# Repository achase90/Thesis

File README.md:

Thesis
======

Folder for my thesis

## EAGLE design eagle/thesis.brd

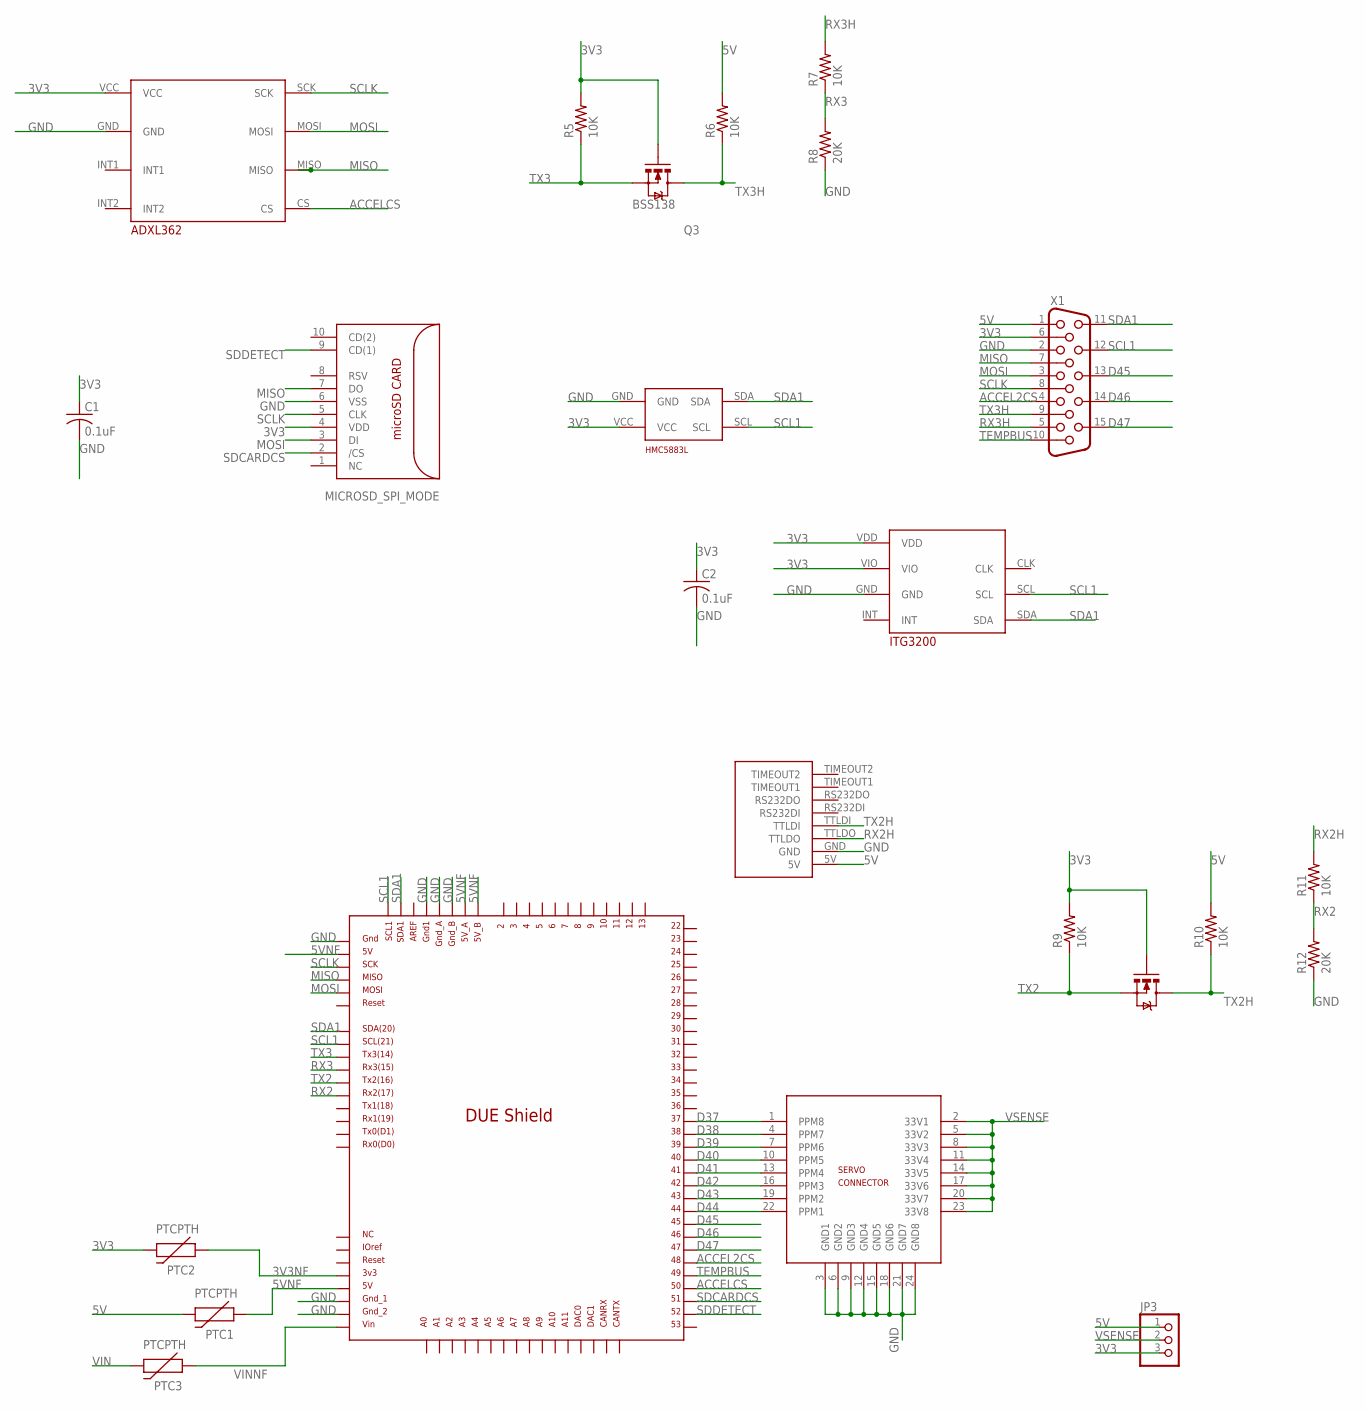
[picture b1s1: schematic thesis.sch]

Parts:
C1, C2: 0.1uF; C0603
JP3: PINHD-1X3; 1X03
PTC1, PTC2, PTC3: PTCPTH; PTC
Q1, Q3: BSS138; SOT23
R5, R6, R7, R9, R10, R11: 10K; R0603
R8, R12: 20K; R0603
U$1: DUE(NORMAL)
U$2: MICROSD_SPI_MODE; MICRO_SD_CONNECTOR
U$4: HMC5883L
U$5: HEADER-3X8SERVO; 3X8RA
U$6: UBLOXLEA6TBOB
U$7: ITG3200
U$8: ADXL362
X1: HF15V; HDF15V

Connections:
3V3: C1.1, C2.1, JP3.3, PTC2.P$2 (2), Q1.1 (G), Q3.1 (G), R5.2, R9.2, U$2.4 (VDD), U$4.VCC, U$7.VDD, U$7.VIO, U$8.VCC, X1.6
3V3NF: PTC2.P$1 (1), U$1.3V3
5V: JP3.1, PTC1.P$2 (2), R6.2, R10.2, U$6.5V, X1.1
5VNF: PTC1.P$1 (1), U$1.5V, U$1.5V_A, U$1.5V_B, U$1.GND_ICSP
ACCEL2CS: U$1.48, X1.4
ACCELCS: U$1.50, U$8.CS
D37: U$1.37, U$5.1 (PPM8)
D38: U$1.38, U$5.4 (PPM7)
D39: U$1.39, U$5.7 (PPM6)
D40: U$1.40, U$5.10 (PPM5)
D41: U$1.41, U$5.13 (PPM4)
D42: U$1.42, U$5.16 (PPM3)
D43: U$1.43, U$5.19 (PPM2)
D44: U$1.44, U$5.22 (PPM1)
D45: U$1.45, X1.13
D46: U$1.46, X1.14
D47: U$1.47, X1.15
GND: C1.2, C2.2, R8.1, R12.1, U$1.5V_ICSP, U$1.GND1, U$1.GND_1, U$1.GND_2, U$1.GND_A, U$1.GND_B, U$2.6 (VSS), U$4.GND, U$5.3 (GND1), U$5.6 (GND2), U$5.9 (GND3), U$5.12 (GND4), U$5.15 (GND5), U$5.18 (GND6), U$5.21 (GND7), U$5.24 (GND8), U$6.GND, U$7.GND, U$8.GND, X1.2
MISO: U$1.MISO_ICSP, U$2.7 (DO), U$8.MISO, X1.7
MOSI: U$1.MOSI_ICSP, U$2.3 (DI), U$8.MOSI, X1.3
RX2: R11.1, R12.2, U$1.RX2
RX2H: R11.2, U$6.TTLDO
RX3: R7.1, R8.2, U$1.RX3
RX3H: R7.2, X1.5
SCL1: U$1.SCL, U$1.SCL1, U$4.SCL, U$7.SCL, X1.12
SCLK: U$1.SCK_ICSP, U$2.5 (CLK), U$8.SCK, X1.8
SDA1: U$1.SDA, U$1.SDA1, U$4.SDA, U$7.SDA, X1.11
SDCARDCS: U$1.51, U$2.2 (/CS)
SDDETECT: U$1.52, U$2.9 (CD(1))
TEMPBUS: U$1.49, X1.10
TX2: Q1.2 (S), R9.1, U$1.TX2
TX2H: Q1.3 (D), R10.1, U$6.TTLDI
TX3: Q3.2 (S), R5.1, U$1.TX3
TX3H: Q3.3 (D), R6.1, X1.9
VIN: PTC3.P$2 (2)
VINNF: PTC3.P$1 (1), U$1.VIN
VSENSE: JP3.2, U$5.2 (33V1), U$5.5 (33V2), U$5.8 (33V3), U$5.11 (33V4), U$5.14 (33V5), U$5.17 (33V6), U$5.20 (33V7), U$5.23 (33V8)

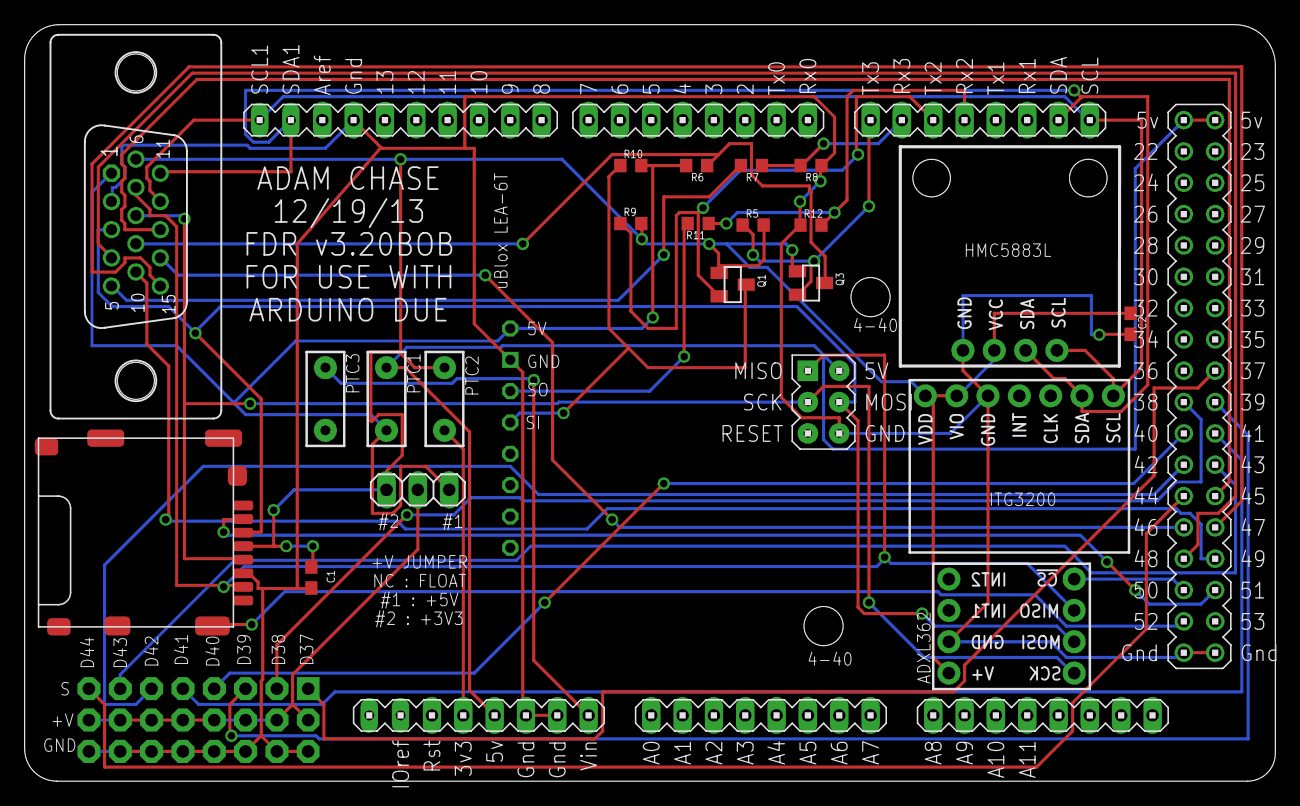
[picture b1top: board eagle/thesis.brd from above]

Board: 2 copper layers, 101.4 x 61.3 mm, 24 parts (0 on the bottom side), 36 nets.

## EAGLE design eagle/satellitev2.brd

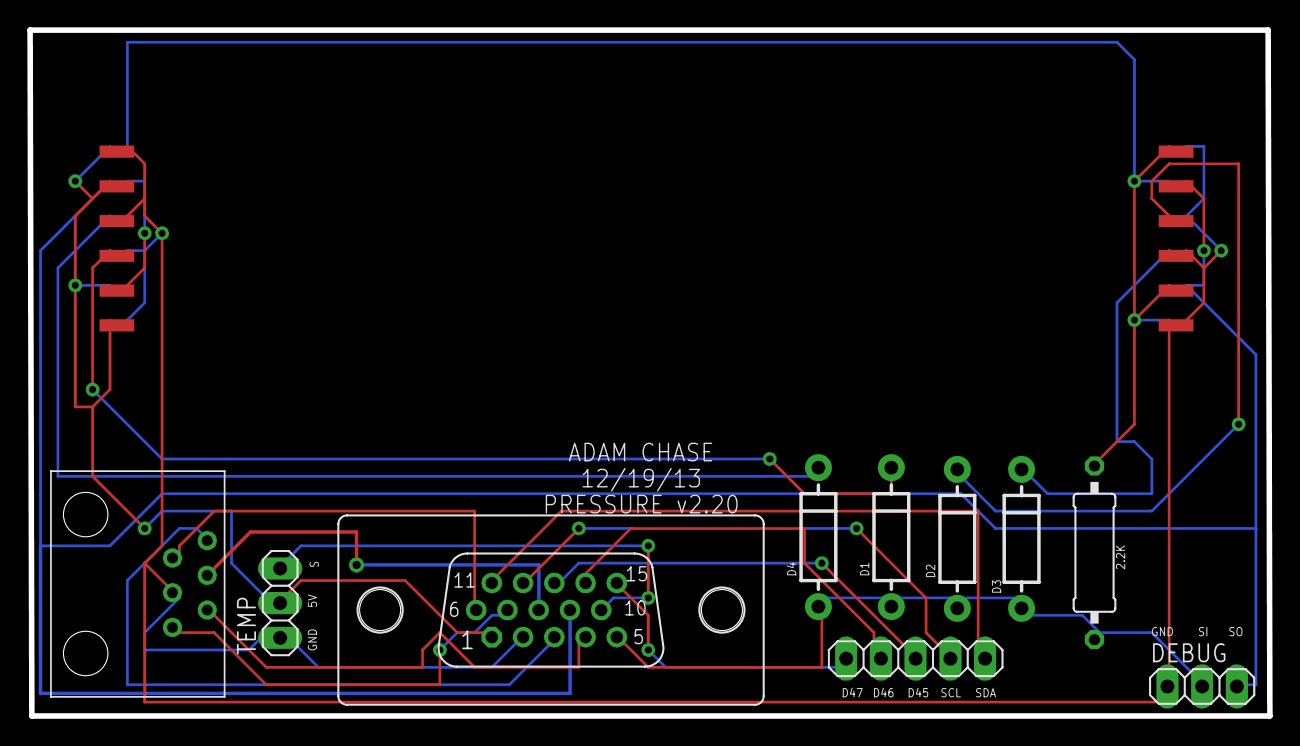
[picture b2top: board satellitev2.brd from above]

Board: 2 copper layers, 90.7 x 50.2 mm, 14 parts (0 on the bottom side), 19 nets.

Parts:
D1, D2, D3, D4: DIODE-1N4001
DEBUG: 1X03
JP1: 1X05
R1: 2.2K; 0309/12
TEMP: 1X03
U$1, U$2: 1X6SMDPINS
U$3, U$4: 1X6SMDPINSB
U$5: RJ11V
X1: HDF15V

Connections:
3V3: U$5.P$6, X1.6
5V: R1.1, TEMP.2, U$1.P$2, U$1.P$6, U$2.P$1, U$2.P$5, U$3.P$2, U$3.P$6, U$4.P$1, U$4.P$5, X1.1
ACCEL2CS: U$5.P$1, X1.4
D45: JP1.3, X1.13
D46: JP1.4, X1.14
D47: JP1.5, X1.15
GND: DEBUG.1, TEMP.1, U$1.P$1, U$1.P$3, U$2.P$4, U$2.P$6, U$3.P$1, U$3.P$3, U$4.P$4, U$4.P$6, U$5.P$5, X1.2
MISO: U$5.P$4, X1.7
MOSI: U$5.P$3, X1.3
unnamed: D2.C, U$2.P$3
unnamed: D1.C, U$1.P$4
unnamed: D4.C, U$4.P$3
unnamed: D3.C, U$3.P$4
RX: DEBUG.3, U$1.P$5, U$2.P$2, U$3.P$5, U$4.P$2, X1.9
SCL: JP1.2, X1.12
SCLK: U$5.P$2, X1.8
SDA: JP1.1, X1.11
TEMPBUS: TEMP.3, X1.10
TX: D1.A, D2.A, D3.A, D4.A, DEBUG.2, R1.2, X1.5

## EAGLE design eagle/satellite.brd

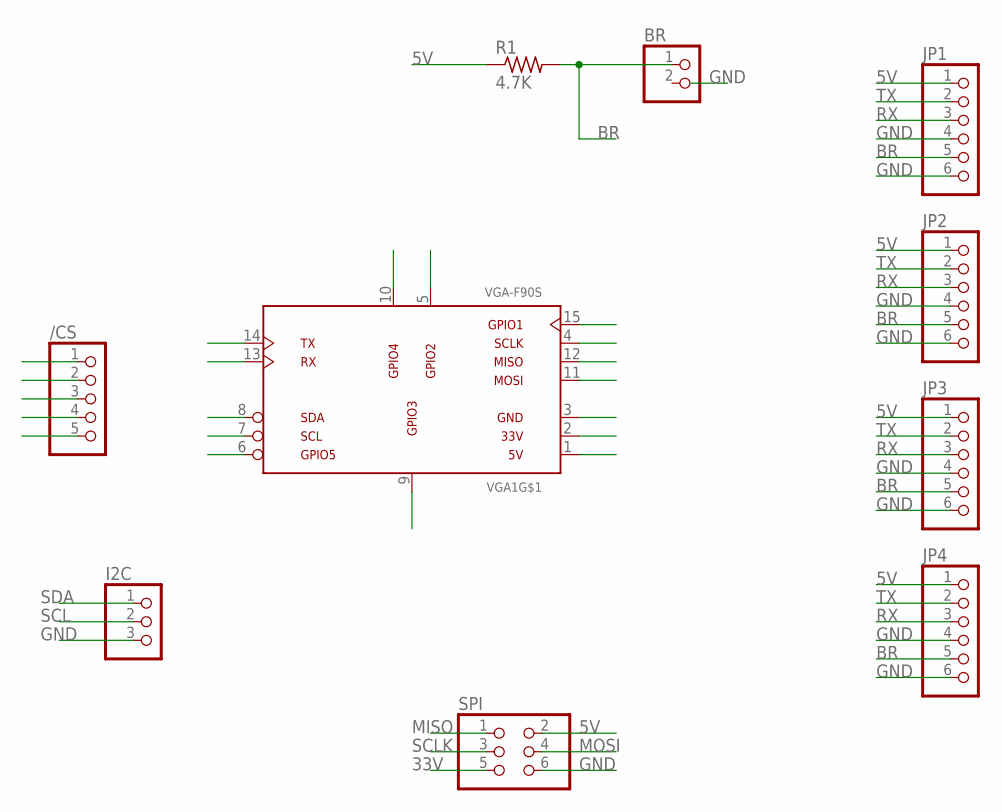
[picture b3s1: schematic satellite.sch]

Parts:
/CS: PINHD-1X5; 1X05
BR: PINHD-1X2; 1X02
I2C: PINHD-1X3; 1X03
JP1, JP2, JP3, JP4: PINHD-1X6; 1X06
R1: 4.7K; 0204/5
SPI: PINHD-2X3; 2X03
VGA1: VGA-F90S; DB-15-F90+SHIELD-SMALL_PADS

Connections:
5V: JP1.1, JP2.1, JP3.1, JP4.1, R1.1, SPI.2, VGA1.1 (VGA-R)
33V: SPI.5, VGA1.2 (VGA-G)
BR: BR.1, JP1.5, JP2.5, JP3.5, JP4.5, R1.2
GND: I2C.3, JP1.4, JP1.6, JP2.4, JP2.6, JP3.4, JP3.6, JP4.4, JP4.6, SPI.6, VGA1.3 (VGA-B)
GPIO1: /CS.1, VGA1.15 (ID3/SCL)
GPIO2: /CS.2, VGA1.5 (GND)
GPIO3: /CS.3, VGA1.9 (+5V)
GPIO4: /CS.4, VGA1.10 (GND)
GPIO5: /CS.5, VGA1.6 (VGA-R-)
MISO: SPI.1, VGA1.12 (ID1/SDA)
MOSI: SPI.4, VGA1.11 (ID0/RES)
RX: JP1.3, JP2.3, JP3.3, JP4.3, VGA1.13 (VGA-HSYNC)
SCL: I2C.2, VGA1.7 (VGA-G-)
SCLK: SPI.3, VGA1.4 (ID2/RES)
SDA: I2C.1, VGA1.8 (VGA-B-)
TX: JP1.2, JP2.2, JP3.2, JP4.2, VGA1.14 (VGA-VSYNC)

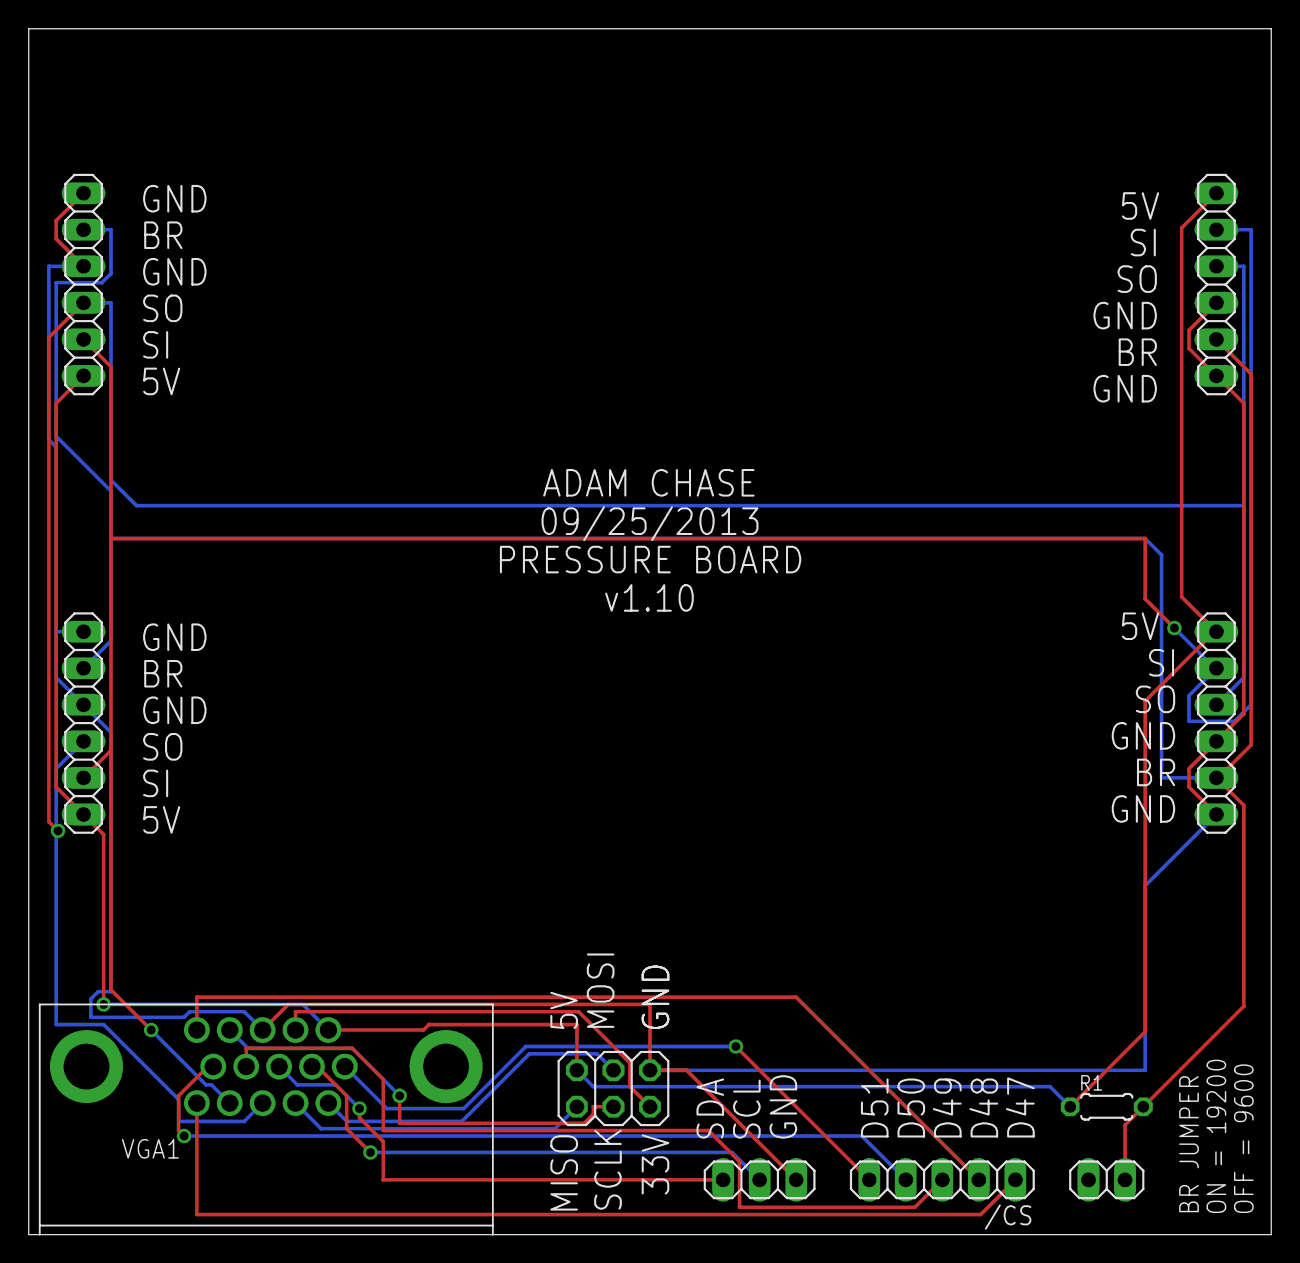
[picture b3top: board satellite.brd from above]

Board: 2 copper layers, 86.4 x 83.8 mm, 10 parts (0 on the bottom side), 16 nets.

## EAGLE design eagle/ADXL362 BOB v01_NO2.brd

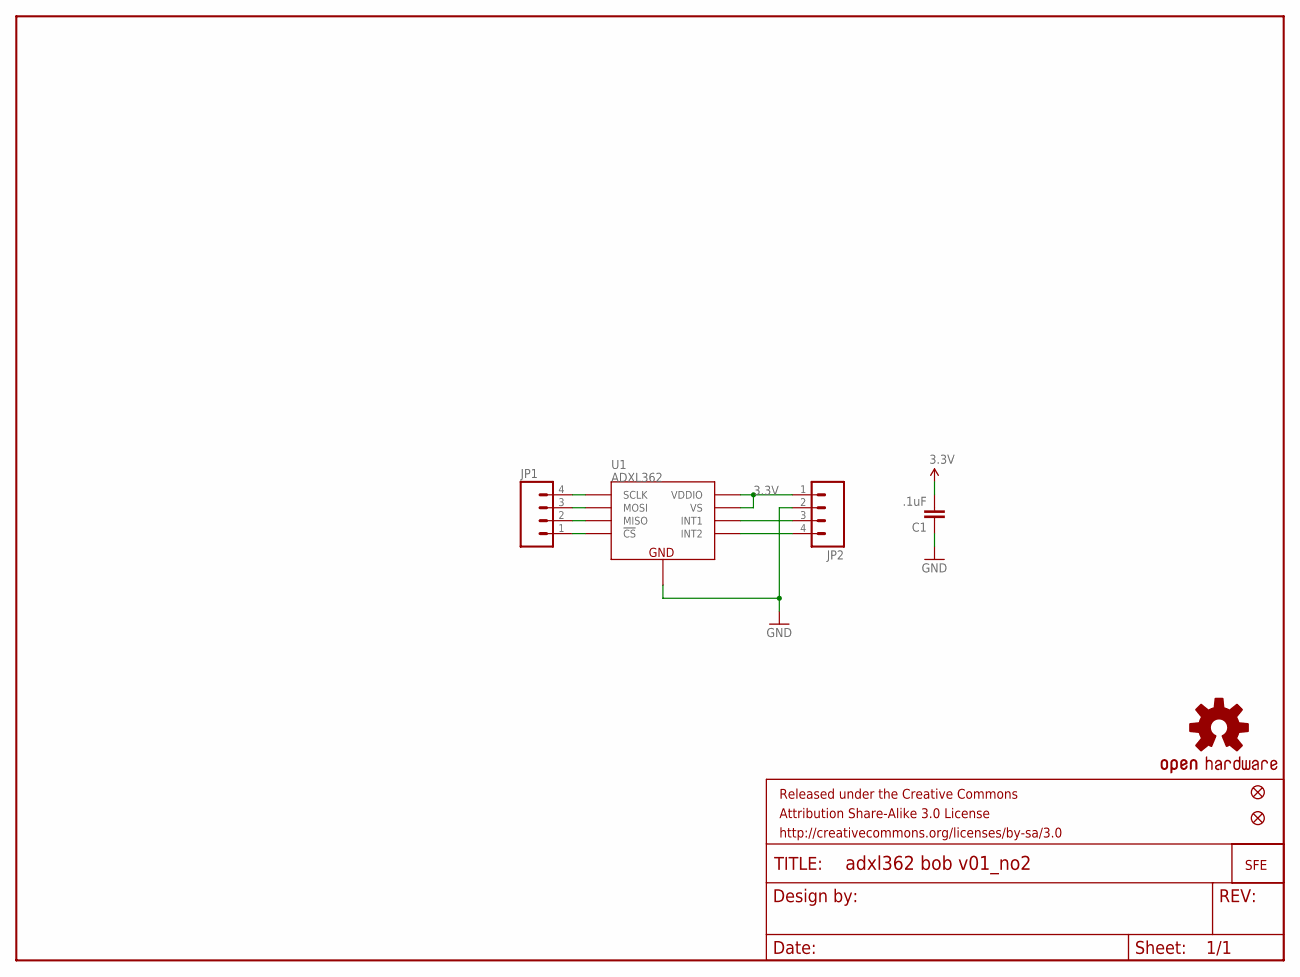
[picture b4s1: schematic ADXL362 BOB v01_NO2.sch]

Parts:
C1: .1uF; 0402-CAP
FRAME1: FRAME-LETTER; CREATIVE_COMMONS
JP1, JP2: M04PTH; 1X04
JP3: LOGO-SFESK; SFE-LOGO-FLAME
JP4, JP5: FIDUCIALUFIDUCIAL; MICRO-FIDUCIAL
U1: ADXL362
U$1: OSHW-LOGOS; OSHW-LOGO-S

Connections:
3.3V: C1.2, JP2.1, U1.P$1 (VDDIO), U1.P$14 (VS)
GND: C1.1, JP2.2, U1.P$12 (GND), U1.P$13 (GND), U1.P$16 (GND)
unnamed: JP1.4, U1.P$4 (SCLK)
unnamed: JP1.3, U1.P$6 (MOSI)
unnamed: JP1.2, U1.P$7 (MISO)
unnamed: JP1.1, U1.P$8 (!CS)
unnamed: JP2.3, U1.P$11 (INT1)
unnamed: JP2.4, U1.P$9 (INT2)

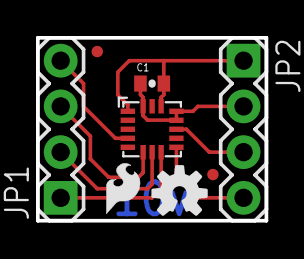
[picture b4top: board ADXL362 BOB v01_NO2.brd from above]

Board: 2 copper layers, 12.7 x 10.2 mm, 9 parts (0 on the bottom side), 8 nets.

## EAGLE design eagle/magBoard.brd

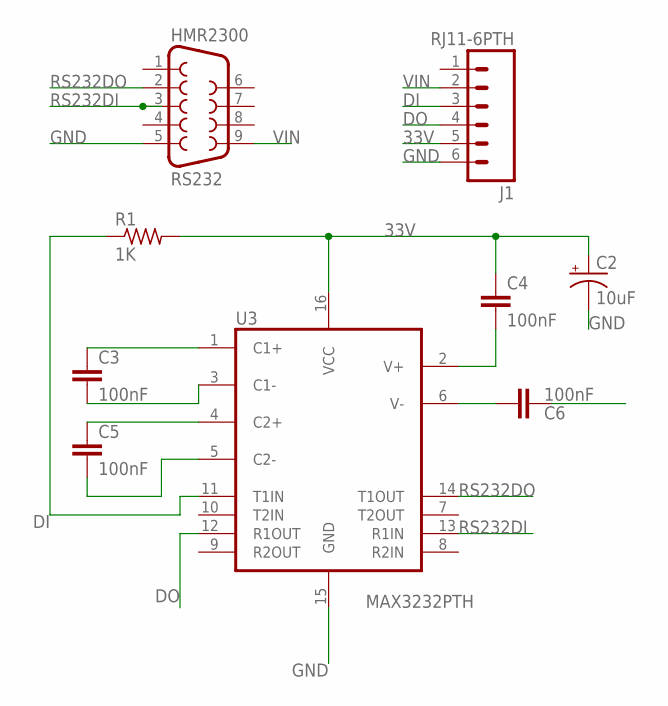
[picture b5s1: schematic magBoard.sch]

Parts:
C2: 10uF; CPOL-RADIAL-10UF-25V
C3, C4, C5, C6: 100nF; CAP-PTH-SMALL-KIT
HMR2300: RS232; DB9
J1: RJ11-6PTH; RJ11-6
R1: 1K; 0204/5
U3: MAX3232PTH; DIL16

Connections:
33V: C2.1 (+), C4.1, J1.5, R1.2, U3.16 (VCC)
DI: J1.3, R1.1, U3.11 (T1IN)
DO: J1.4, U3.12 (R1OUT)
GND: C2.2 (-), C6.2, HMR2300.5, J1.6, U3.15 (GND)
unnamed: C3.1, U3.1 (C1+)
unnamed: C3.2, U3.3 (C1-)
unnamed: C5.1, U3.4 (C2+)
unnamed: C5.2, U3.5 (C2-)
unnamed: C4.2, U3.2 (V+)
unnamed: C6.1, U3.6 (V-)
RS232DI: HMR2300.3, U3.13 (R1IN)
RS232DO: HMR2300.2, U3.14 (T1OUT)
VIN: HMR2300.9, J1.2

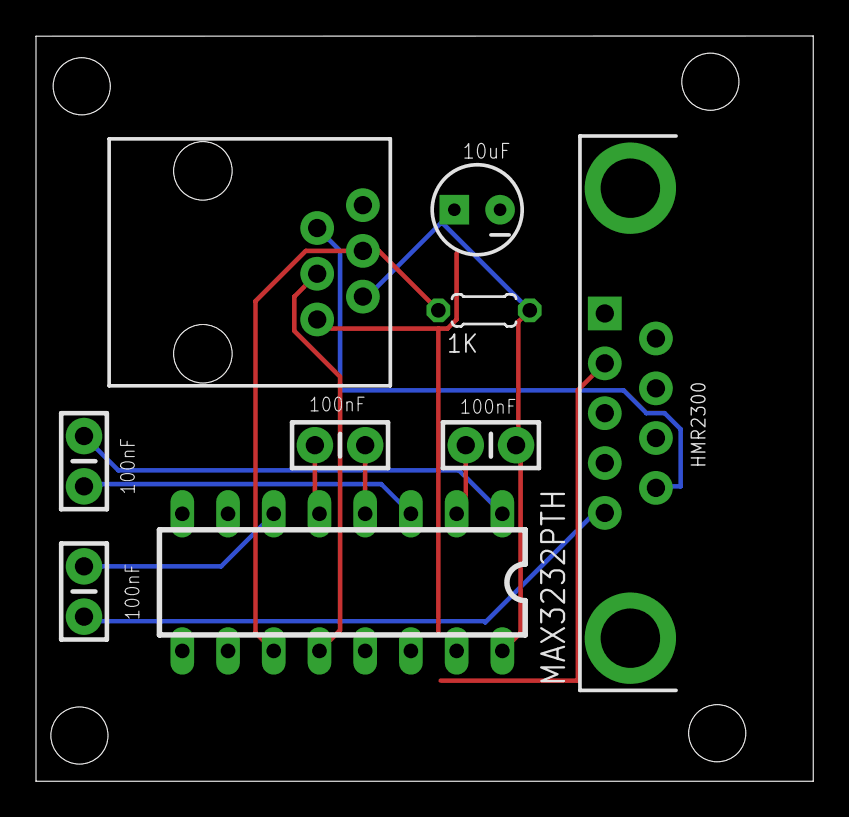
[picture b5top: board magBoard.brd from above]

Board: 2 copper layers, 43.2 x 41.4 mm, 9 parts (0 on the bottom side), 13 nets.

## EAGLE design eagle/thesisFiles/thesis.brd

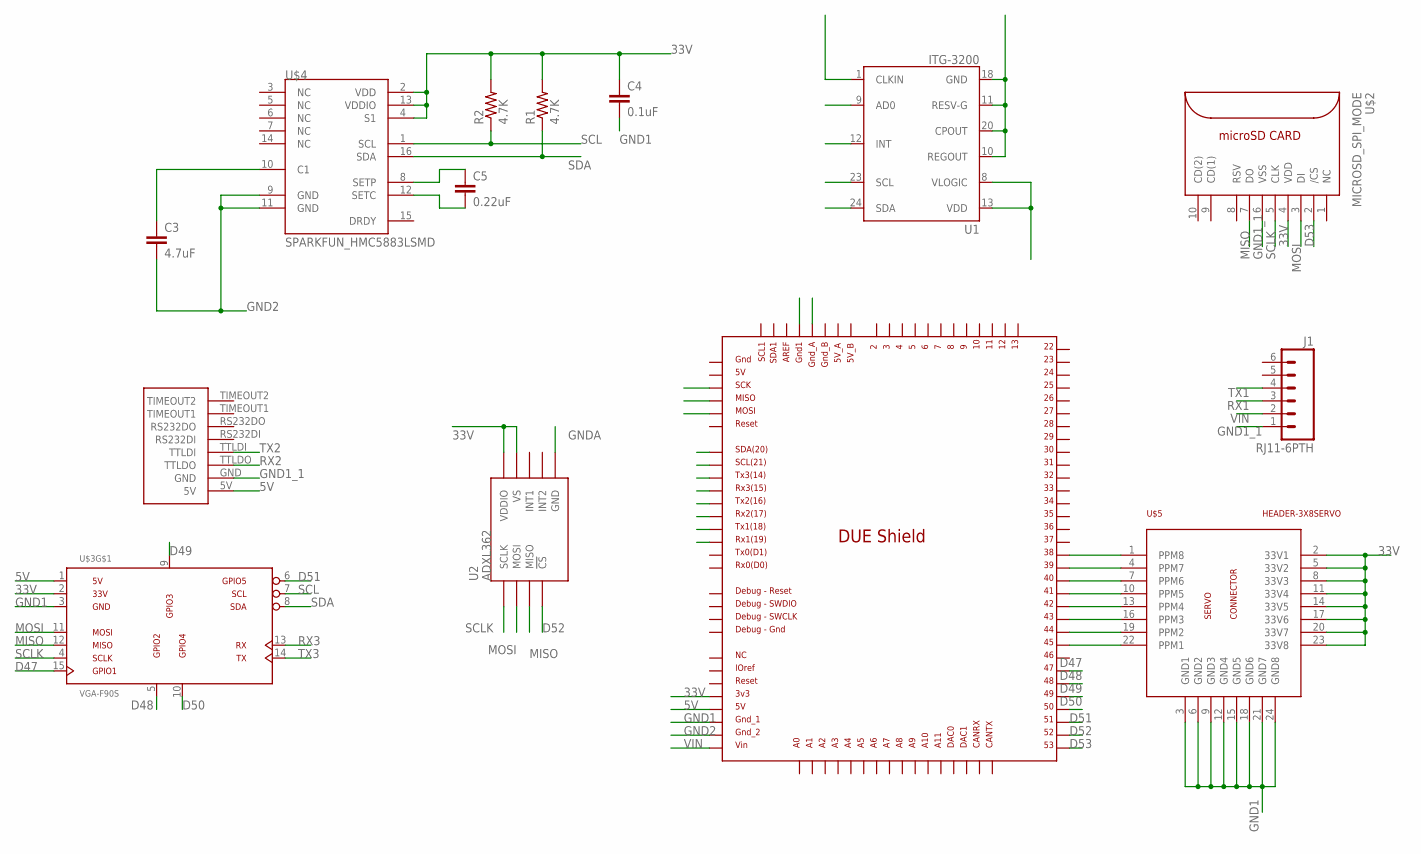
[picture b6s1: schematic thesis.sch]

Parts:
C3: 4.7uF; SPARKFUN_0402-CAP
C4: 0.1uF; SPARKFUN_0402-CAP
C5: 0.22uF; SPARKFUN_0402-CAP
J1: RJ11-6PTH; RJ11-6
R1, R2: 4.7K; SPARKFUN_0402-RES
U1: ITG-3200; QFN-24
U2: ADXL362
U$1: DUE(NORMAL)
U$2: MICROSD_SPI_MODE; MICRO_SD_CONNECTOR
U$3: VGA-F90S; DB-15-F90+SHIELD-SMALL_PADS
U$4: SPARKFUN_HMC5883LSMD; SPARKFUN_16LPCC
U$5: HEADER-3X8SERVO; 3X8RA
U$6: UBLOXLEA6TBOB

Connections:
5V: U$1.5V, U$3.1 (VGA-R), U$6.5V
33V: C4.1, R1.2, R2.2, U1.8 (VLOGIC), U1.9 (AD0), U1.13 (VDD), U2.P$1 (VDDIO), U2.P$14 (VS), U$1.3V3, U$2.4 (VDD), U$3.2 (VGA-G), U$4.2 (VDD), U$4.4 (S1), U$4.13 (VDDIO), U$5.2 (33V1), U$5.5 (33V2), U$5.8 (33V3), U$5.11 (33V4), U$5.14 (33V5), U$5.17 (33V6), U$5.20 (33V7), U$5.23 (33V8)
D47: U$1.47, U$3.15 (ID3/SCL)
D48: U$1.48, U$3.5 (GND)
D49: U$1.49, U$3.9 (+5V)
D50: U$1.50, U$3.10 (GND)
D51: U$1.51, U$3.6 (VGA-R-)
D52: U2.P$8 (!CS), U$1.52
D53: U$1.53, U$2.2 (/CS)
GND1: C4.2, U$1.GND_1, U$3.3 (VGA-B), U$5.3 (GND1), U$5.6 (GND2), U$5.9 (GND3), U$5.12 (GND4), U$5.15 (GND5), U$5.18 (GND6), U$5.21 (GND7), U$5.24 (GND8)
GND1_1: J1.1, U$1.GND1, U$2.6 (VSS), U$6.GND
GND2: C3.2, U$1.GND_2, U$4.9 (GND), U$4.11 (GND)
GNDA: U1.1 (CLKIN), U1.10 (REGOUT), U1.11 (RESV-G), U1.12 (INT), U1.18 (GND), U1.20 (CPOUT), U2.P$12 (GND), U2.P$13 (GND), U2.P$16 (GND), U$1.GND_A
MISO: U2.P$7 (MISO), U$1.MISO_ICSP, U$2.7 (DO), U$3.12 (ID1/SDA)
MOSI: U2.P$6 (MOSI), U$1.MOSI_ICSP, U$2.3 (DI), U$3.11 (ID0/RES)
unnamed: U$1.38, U$5.1 (PPM8)
unnamed: U$1.39, U$5.4 (PPM7)
unnamed: U$1.40, U$5.7 (PPM6)
unnamed: U$1.41, U$5.10 (PPM5)
unnamed: C5.1, U$4.8 (SETP)
unnamed: U$1.42, U$5.13 (PPM4)
unnamed: C5.2, U$4.12 (SETC)
unnamed: U$1.43, U$5.16 (PPM3)
unnamed: U$1.44, U$5.19 (PPM2)
unnamed: U$1.45, U$5.22 (PPM1)
unnamed: C3.1, U$4.10 (C1)
RX1: J1.3, U$1.RX1
RX2: U$1.RX2, U$6.TTLDO
RX3: U$1.RX3, U$3.13 (VGA-HSYNC)
SCL: R2.1, U1.23 (SCL), U$1.SCL, U$3.7 (VGA-G-), U$4.1 (SCL)
SCLK: U2.P$4 (SCLK), U$1.SCK_ICSP, U$2.5 (CLK), U$3.4 (ID2/RES)
SDA: R1.1, U1.24 (SDA), U$1.SDA, U$3.8 (VGA-B-), U$4.16 (SDA)
TX1: J1.4, U$1.TX1
TX2: U$1.TX2, U$6.TTLDI
TX3: U$1.TX3, U$3.14 (VGA-VSYNC)
VIN: J1.2, U$1.VIN

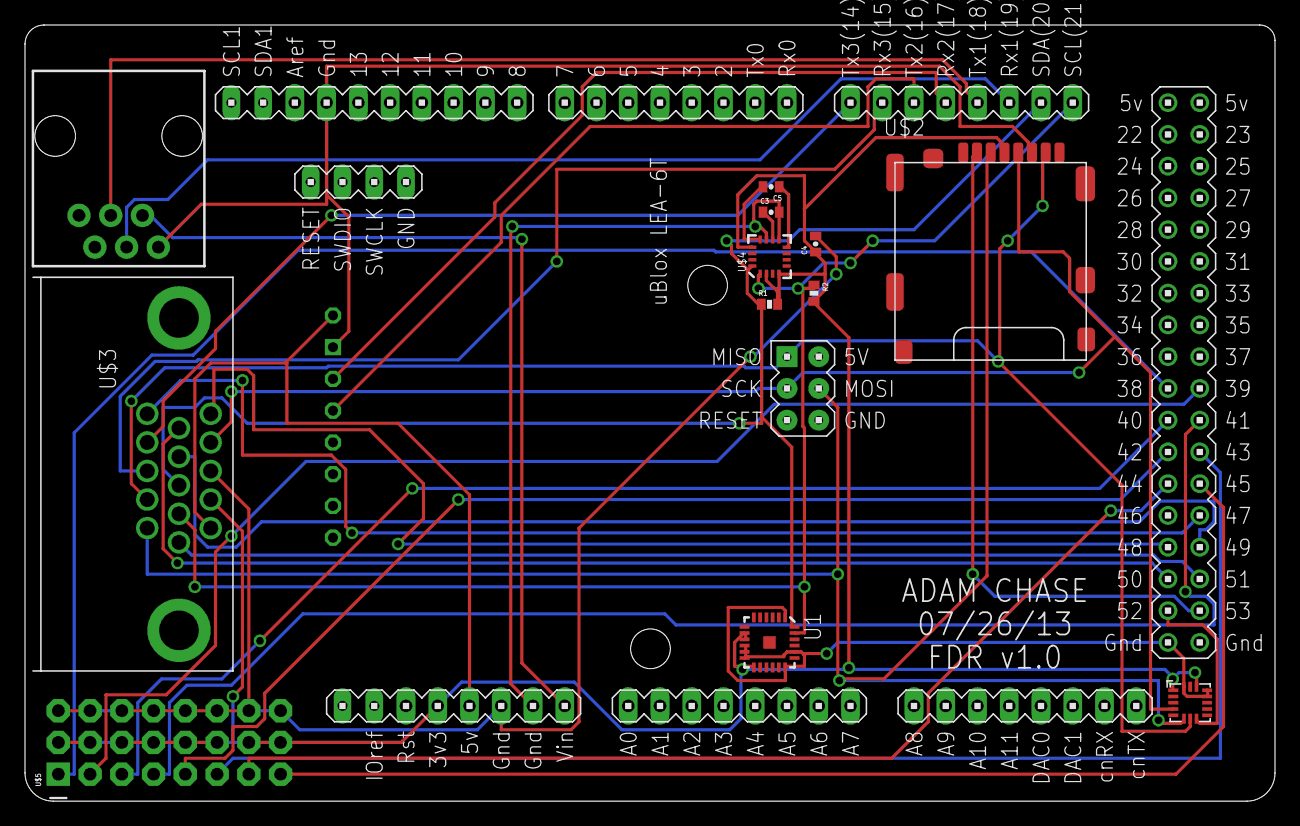
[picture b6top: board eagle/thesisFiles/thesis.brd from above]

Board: 2 copper layers, 100.0 x 62.1 mm, 14 parts (0 on the bottom side), 36 nets.

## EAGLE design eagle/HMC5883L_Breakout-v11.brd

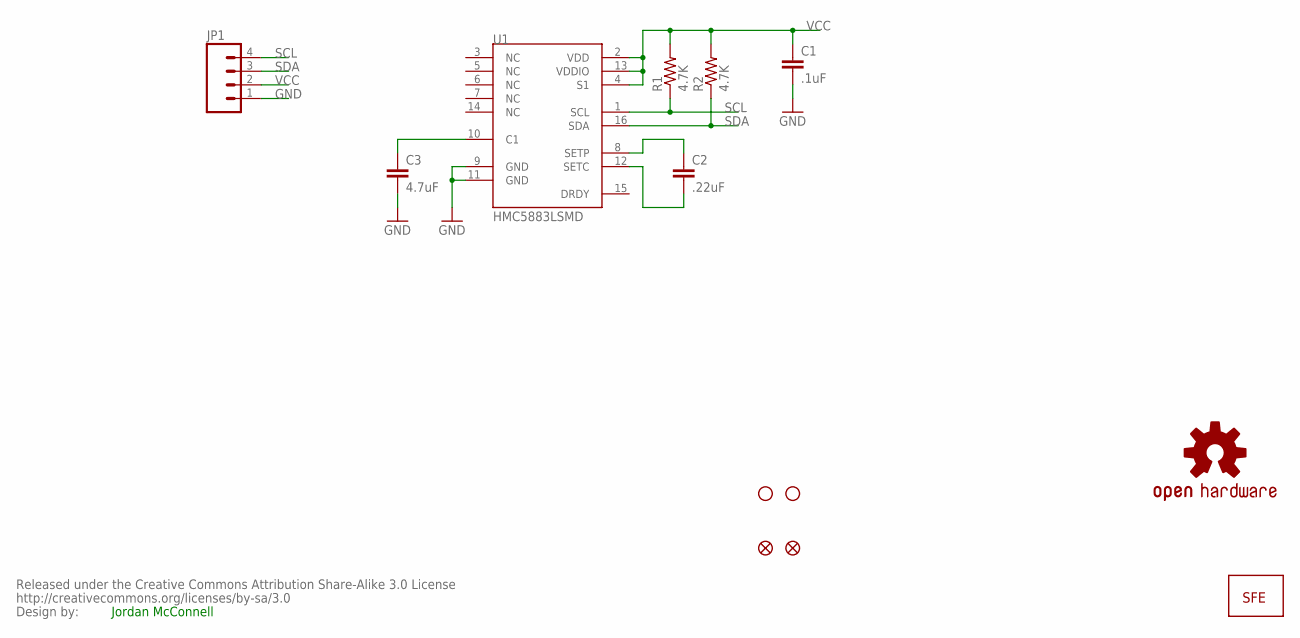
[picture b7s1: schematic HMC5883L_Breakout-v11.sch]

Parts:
C1: .1uF; 0402-CAP
C2: .22uF; 0402-CAP
C3: 4.7uF; 0402-CAP
JP1: M04PTH; 1X04
JP2, JP3: STAND-OFF
JP4: LOGO-SFESK; SFE-LOGO-FLAME
JP5, JP6: FIDUCIAL1X2.5; FIDUCIAL-1X2.5
R1, R2: 4.7K; 0402-RES
U1: HMC5883LSMD; 16LPCC
U$1: CREATIVE_COMMONS
U$2: OSHW-LOGOM; OSHW-LOGO-M

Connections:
GND: C1.2, C3.2, JP1.1, U1.9 (GND), U1.11 (GND)
unnamed: C3.1, U1.10 (C1)
unnamed: C2.1, U1.8 (SETP)
unnamed: C2.2, U1.12 (SETC)
SCL: JP1.4, R1.1, U1.1 (SCL)
SDA: JP1.3, R2.1, U1.16 (SDA)
VCC: C1.1, JP1.2, R1.2, R2.2, U1.2 (VDD), U1.4 (S1), U1.13 (VDDIO)

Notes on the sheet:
Jordan McConnell

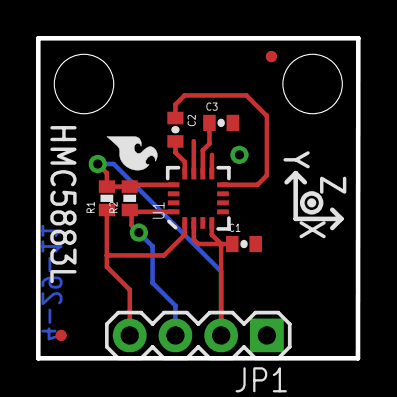
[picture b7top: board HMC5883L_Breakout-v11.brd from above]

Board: 2 copper layers, 17.8 x 17.8 mm, 14 parts (1 on the bottom side), 7 nets.

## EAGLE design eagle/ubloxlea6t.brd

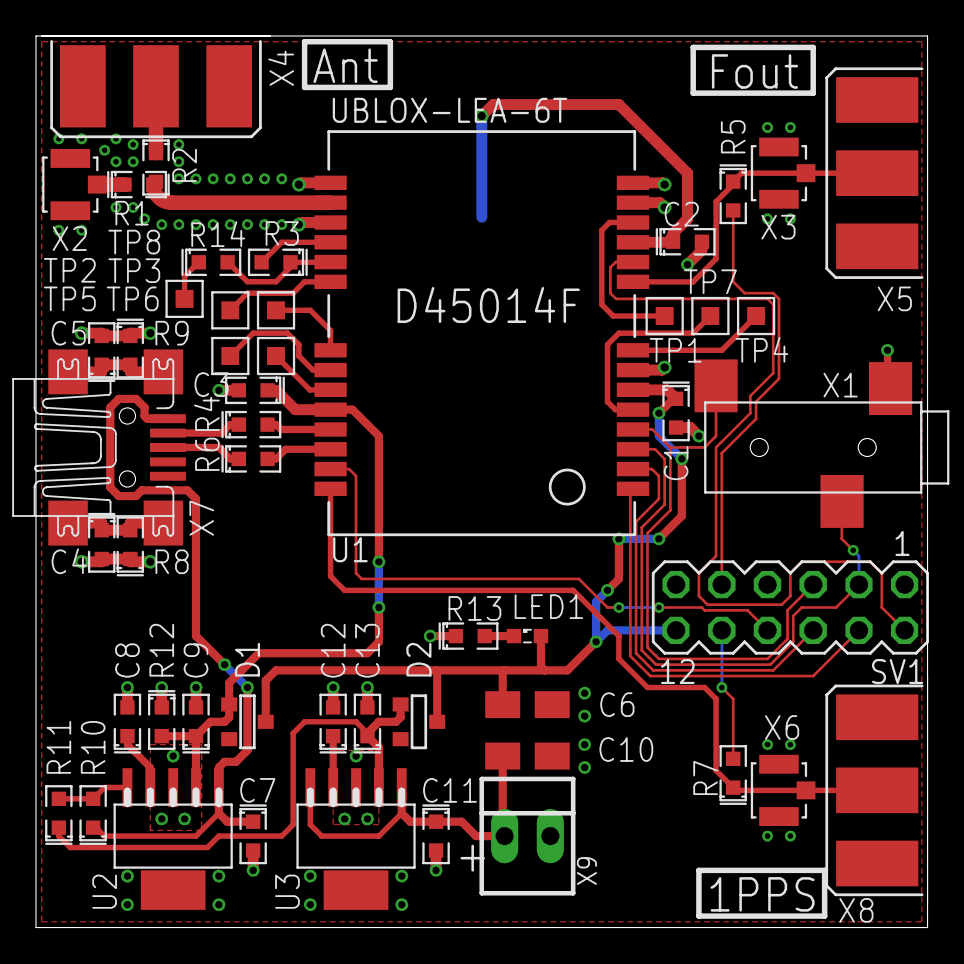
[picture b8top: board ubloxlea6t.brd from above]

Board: 2 copper layers, 49.5 x 49.5 mm, 52 parts (1 on the bottom side), 40 nets.

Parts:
B1: SMTU2032-LF; SMTU2032
C1, C3, C4, C5: 100n; 0603
C2: DNP; 0603
C6, C10: 10u; A/3216-18R
C7, C9, C11, C13: 1u; 0603
C8, C12: 10n; 0603
D1, D2: BAT54; SOT23
LED1: SML0603
R1, R2, R5, R7: 0R; 0603
R3: 10R; 0603
R4, R6: 22R; 0603
R8, R9: 1M; 0603
R10: 1k; 0603
R11, R12, R14: DNP; 0603
R13: 0603
SV1: MA06-2
TP1, TP2, TP3, TP4, TP5, TP6, TP7, TP8: TESTPAD; TP_1X1
U1: UBLOX-LEA-6T; UBLOX-LEA-6
U2, U3: TPS73633; SOT223-6
X1: SERIAL; JACK2.5_SJ-2523
X2: ANT; HRS_UFL
X3: FOUT; HRS_UFL
X4: ANT; SMA-F-S-EDGE
X5: FOUT; SMA-F-S-EDGE
X6: 1PPS; HRS_UFL
X7: PC; UX60-MB-5ST
X8: 1PPS; SMA-F-S-EDGE
X9: 22-23-2021

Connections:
1PPS: R7.1, U1.28, X6.SIG, X8.C
1PPS_EXT: R7.2, SV1.10
3V3: C1.1, C6.+, D1.3, D2.3, LED1.A, SV1.12, U1.6
!RESET: SV1.2, U1.10
FOUT: R5.1, U1.9, X3.SIG, X5.C
FOUT_EXT: R5.2, SV1.9
GND: B1.-, C1.2, C2.2, C3.2, C4.2, C5.2, C6.-, C7.2, C8.2, C9.2, C10.-, C11.2, C12.2, C13.2, R8.1, R9.1, R12.1, R13.1, SV1.1, SV1.7, SV1.11, U1.7, U1.13, U1.14, U1.15, U1.17, U2.3, U2.6, U3.3, U3.6, X1.1, X2.GND@1, X2.GND@2, X3.GND@1, X3.GND@2, X4.BG1, X4.BG2, X4.TG1, X4.TG2, X5.BG1, X5.BG2, X5.TG1, X5.TG2, X6.GND@1, X6.GND@2, X7.5, X8.BG1, X8.BG2, X8.TG1, X8.TG2, X9.2
INT: SV1.8, U1.27
unnamed: R2.1, X4.C
unnamed: C4.1, R8.2, X7.M1, X7.M4
unnamed: R4.2, U1.25
unnamed: R6.2, U1.26
unnamed: R3.2, U1.18
unnamed: R3.1, R14.2, U1.19
unnamed: TP3.TP, U1.21
unnamed: TP2.TP, U1.20
unnamed: TP5.TP, U1.22
unnamed: TP6.TP, U1.23
unnamed: R6.1, X7.3
unnamed: R4.1, X7.2
unnamed: C8.1, U2.4
unnamed: TP1.TP, U1.12
unnamed: B1.+, C2.1, U1.11
unnamed: R1.1, X2.SIG
unnamed: TP4.TP, U1.8
unnamed: TP7.TP, U1.5
unnamed: R1.2, R2.2, U1.16
unnamed: C5.1, R9.2, X7.M2, X7.M3
unnamed: C10.+, C11.1, U3.1, U3.5, X9.1
unnamed: C12.1, U3.4
unnamed: C13.1, D2.1, R11.1, U3.2
unnamed: R10.2, R11.2, U2.5
unnamed: LED1.C, R13.2
unnamed: R14.1, TP8.TP
SCL: SV1.6, U1.2
SDA: SV1.4, U1.1
SERIAL_RXD: SV1.5, U1.4, X1.2
SERIAL_TXD: SV1.3, U1.3, X1.3
VBUS: C7.1, R10.1, U2.1, X7.1
VUSB: C3.1, C9.1, D1.1, R12.2, U1.24, U2.2

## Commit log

2013-07-09 Initial repo commit
2013-07-09 Added back the old git repo with cleaned up files.
2013-07-09 added honeywell drivers and db9 solidworks model
2013-07-10 modified db9 connector
2013-07-11 going home for the day. nothing in here works any better than before.
2013-07-12 made changes to eagle files
2013-07-12 added satellite board and thesis project
2013-07-17 modified proposal presentation and added two new images
2013-07-17 create mainScript folder and script
2013-07-18 modified arduino scripts
2013-07-19 modified accel function to get it working
2013-07-19 modified accel to take into account FS range and return values for XYZT
2013-07-23 got compass working
2013-07-23 converted compass output to binary
2013-07-23 got pressure sensors working
2013-07-24 pressure transducer now outputs data in integer form
2013-07-25 got fixed point gps processing working, but it's slower than using floating point, at least for the arduino due, so switching to atof
2013-07-25 switching to atof version of parsing gps data, since it's faster on the arduino due
2013-07-25 gps parsed and outputting integer values
2013-07-25 final changes to gps parser file.
2013-07-25 pressure sensors working with unique read commands
2013-07-25 multiple pressure sensors working on the same serial bus
2013-07-25 cleaned up pressure code
2013-07-25 cleaned up gps code
2013-07-25 cleaned up magnetometer code
2013-07-26 Cleaned up accel code and fixed ADXL library file
2013-07-26 cleaned out unneeded files in hardware folder and slight modification to gyroTestScript
2013-07-26 magBoard eagle file created
2013-07-26 updated magBoard and thesis files, added a couple boards and schematics for references or parts.
2013-07-26 eagle file changes
2013-07-27 changes to eagle files
2013-07-29 eagle file changes that were submitted for a quote
2013-07-29 added 5 hole probe calibration documents
2013-07-30 bill of materials added and serial device initialization function created
2013-07-30 pressure sensors working
2013-07-30 modified serial port referencing to map to sensors better
2013-07-30 gyro working
2013-07-30 accel working
2013-07-31 gps work
2013-08-01 I think gps is working now
2013-08-01 gps integrated into main script and ready to be written to SD card
2013-08-02 code cleanup
2013-08-02 modified gps msgID for loop
2013-08-02 modified grad seminar ppt
2013-08-02 read in probe calibration data and changed data reading order in main script
2013-08-02 should be working, completely out to files now.
2013-08-03 shit's working yo!
2013-08-04 changed serial comm speeds, switched to buffered SD card writing
2013-08-05 integrated temperature sensor and added some preprocessor defines
2013-08-06 added serial input commands and modified pressure sensors for calibration.
2013-08-06 added magnetometer calibration routine
2013-08-07 fixed serial input and initSD
2013-08-07 modified matlab read in file
2013-08-08 fixed gps and modified fileParser to match
2013-08-08 deleted some test data
2013-08-12 created flight read in and parsing functions based on sim funtions.
2013-08-14 made board revision to v2.0 and ready to order, pending BOM
2013-08-14 modified RJ11 to match crossover cable and got BOM done
2013-08-14 removed AIAA, will add back to that branch later.
2013-08-15 split thesis into multiple individual files and fixed most of hardware section.
2013-08-15 added ribbon drag paper and wrote some validation techniques
2013-08-15 added prandtl and wrote more.
2013-08-18 wrote a bunch and added references and pictures
2013-08-18 added calibration routines
2013-09-29 wrote more.
2013-09-29 added top paste layer for thesis boards
2013-09-30 modified satellite board to fix incorrect routing
2013-09-30 parsed angles to alpha and beta
2013-09-30 Updated satellite board.
2013-10-06 added receipts, wrote a lot, and fixed latex formatting issues.
2013-10-19 wrote a bunch and made figures
2013-10-21 added breakout board libraries and changed thesis.brd
2013-10-21 modified to match perf board serial assignments
2013-10-21 modified thesis boards to include a lot of components
2013-10-21 fixed gps parser bug
2013-10-21 fixed gps parser bug I found in the breakoutboards branch, but I don't know how to cherry pick commits.
2013-10-21 added smaller satellite board
2013-10-21 routed thesis board
2013-10-22 flipped itg3200 board
2013-10-22 modified eagle files, should be ready to order
2013-10-22 changed eagle files.
2013-10-22 added smaller satellite board
    Conflicts:
    eagle/thesis.brd
    eagle/thesis.pro
    eagle/thesis.sch
2013-10-23 modified eagle boards and ordered.
2013-10-23 modified eagle boards, ordered them.
2013-10-23 added BOM from order.
2013-10-25 proto-board working, about to begin software dev for file input and plotting.
2013-10-25 empty gui created
2013-10-26 created UI for file parsing
2013-10-26 messed with beaver file for ui
2013-10-26 a lot of error checking, wrote some unit conversions
2013-10-26 added google earth functionality and made GUI work with complete data file.
2013-10-27 middle of screwed up matlab fig file
2013-10-27 Revert "added google earth functionality and made GUI work with complete data file."
    This reverts commit a37c235de9734745ac1dde432697b19c41522d92.
    Conflicts:
    Flight Analysis/fileReader.m
    Everything seems to be working nicely, got automatic latex strip charts working, gps working, fixed bug with binaryParser.
2013-10-27 changed hmc5883L to be Arduino due compatible.
2013-10-28 got pwmSense working, just started integrating into main script
2013-10-28 implemented pwm measurement, should work. also changed baud rates from const uint32_t to #defines
2013-10-28 more code cleanup
2013-10-28 more cleanup
2013-10-28 final code cleanup
2013-10-28 messed with compassTest
2013-10-28 wrote calibration routine for gyro,accel,and pressure calibration at the field. Need to verify it works, but it compiles.
2013-10-28 moved gui files around and changed how "save" was happening.
2013-10-29 gps seems to be working. now to field separate.
2013-10-29 gps check sum seems to be working.
2013-10-29 added horizon hobby receipt and rpm image for latex
2013-10-30 created 5-hole probe mount in solidworks to be fabbed by ExSys
2013-10-30 gps seems to working reliably.
2013-10-30 increased hole tolerances on pressure mount
2013-10-30 added check sum calculator to main script
2013-10-30 fixed presssure sensor addressing bug
2013-10-30 gps parsing in the main script seems to be working
2013-10-30 added code profiling to time code.
2013-10-31 pseudo code for calcForces callback function
2013-10-31 made a lot of code changes, but everything seems to be working. Modified data structure layout and got things working from binary data to drag polar, except for BS unit conversions and some plant iss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
2013-10-31 changed baud rate and changed some data file serial prints
2013-10-31 fixed file save and a bunch of small stuff, everything seems to be working now.
2013-11-01 changed how strip charts were made to include all data in the GUI. pretty happy with where things are, everything seems to be working.
2013-11-05 added some calibration stuff.
2013-11-05 added mdl file
2013-11-11 modified sim to reflect the need for only accelerometer
2013-11-12 hardware seems to be fully functionin, haven't check mainscript yet
2013-11-13 software seems to be working with all hardware, including outputting pwm rates and second magnetometer
2013-11-22 made a lot of changes and included some calibration processes.
2013-11-22 modified gps board pad drill size and made thesis board a BOB.
2013-11-22 added itg3200
2013-11-27 modified main thesis boards and made changes to the GUI
2013-12-10 in middle of writing for AIAA paper
2013-12-10 updated sim to match accelerometer method
2013-12-10 wrote a bunch
2013-12-11 updated sim to match accelerometer method
    Conflicts:
    Beaver Sim/asbdhc2.mdl
    Beaver Sim/dataReadin.m
    Beaver Sim/mainScript.m
    Beaver Sim/modelScript.m
    Beaver Sim/plant.m
2013-12-11 added SMD schematic and board DXF files for AIAA paper
2013-12-14 final commit for AIAA paper
2013-12-19 removed unnecessary files
2013-12-21 modified latex files to match thesis
2013-12-21 updated latex to merge aiaa and thesis
2013-12-22 wrote a lot of appendices, removed unnecessary honeywell drivers.
2013-12-22 wrote more
2013-12-22 wrote some calibration and added more to the system manual
2013-12-26 created AIAA ppt
2013-12-26 added old dxf files for ppt
2014-01-03 updating gui equations
2014-01-03 changed a lot on how things are calculated in the GUI
2014-01-03 fixed the shitty saved data issue
2014-01-28 BOOM!

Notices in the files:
eagle/ubloxlea6t.brd:
(c) 2012 Munaut
parts and their libraries:
SparkFun-Sensors: Licensing: CC v3.0 Share-Alike You are welcome to use this library for commercial purposes.
SparkFun-Aesthetics: Released under the Creative Commons Attribution Share-Alike 3.0 License
SparkFun-Aesthetics: http://creativecommons.org/licenses/by-sa/3.0
